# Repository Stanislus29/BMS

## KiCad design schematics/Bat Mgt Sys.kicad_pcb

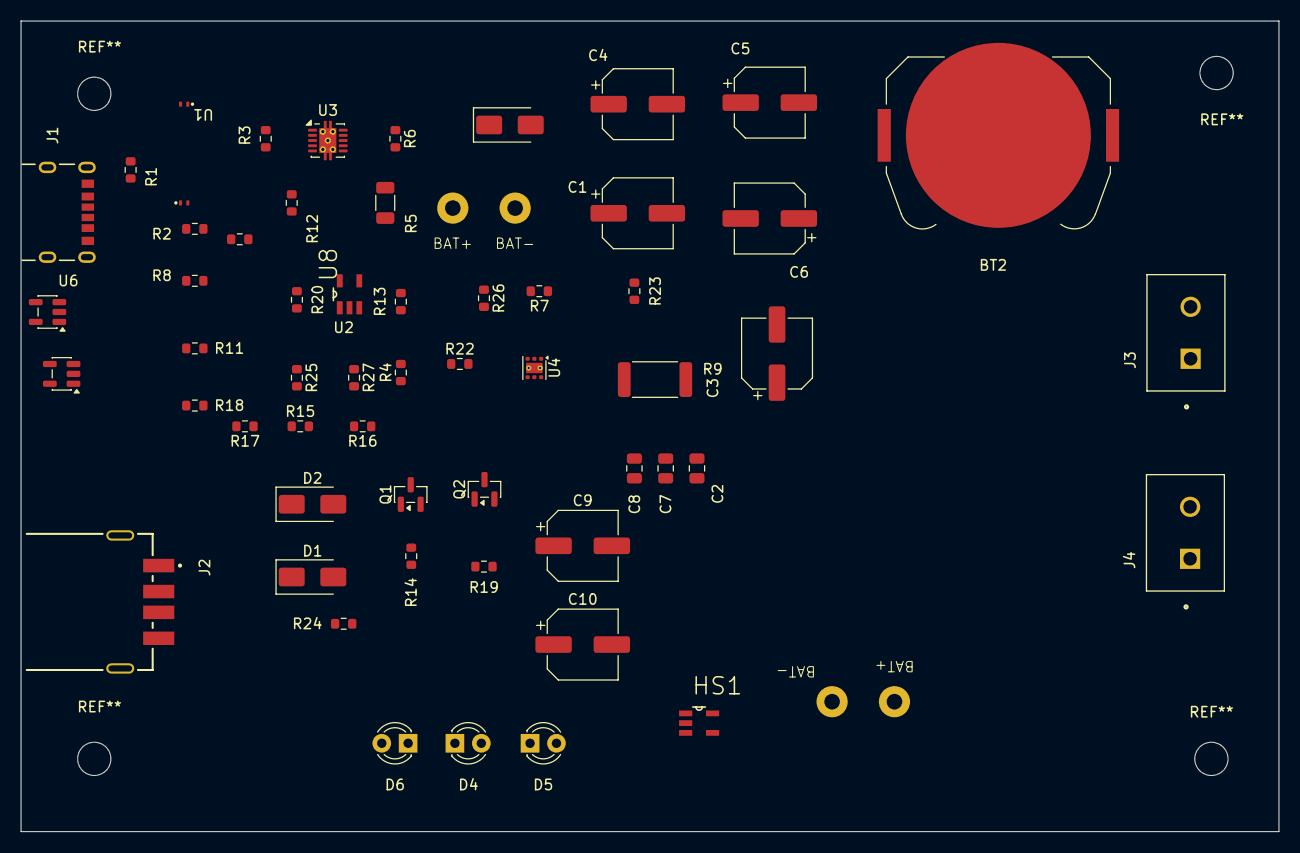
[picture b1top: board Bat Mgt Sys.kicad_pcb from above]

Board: 4 copper layers, 121.0 x 78.0 mm, 59 parts (0 on the bottom side), 29 nets, no tracks yet.

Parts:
BT1: Battery; THROUGH_HOLES
BT2: 2.0; BatteryHolder_Keystone_3034_1x20mm
C1, C4, C6: 100u; CP_Elec_6.3x5.4
C2: 0.1u; C_0805_2012Metric
C3: 22n; CP_Elec_6.3x5.4
C5: 4700u; CP_Elec_6.3x5.4
C7, C8: 10u; C_0805_2012Metric
C9, C10: 22; CP_Elec_6.3x5.4
D1, D2, D3: SS14; D_SMA
D4: GREEN; LED_D3.0mm
D5: RED; LED_D3.0mm
D6: WHITE; LED_D3.0mm
HS1: 5.8 W/mK; SOT95P280X140-5N
J1: USB_C_Receptacle_PowerOnly_6P; MOLEX_2171750001
J2: USB_A; GCT_USB1046-GF-0190-L-B-A_REVB4
J3, J4: Screw_Terminal_01x02; OST_OSTTC020162
Q1, Q2: IRLML6402; SOT-23
R1, R2: 5.1K; R_0603_1608Metric
R3: 1M; R_0603_1608Metric
R4: 453k; R_0603_1608Metric
R5: 1; R_1206_3216Metric
R6: 76.8k; R_0603_1608Metric
R7: 42.25k; R_0603_1608Metric
R8, R14, R15, R16, R18, R22, R24: 10k; R_0603_1608Metric
R9: 0.885; R_2512_6332Metric
R11: 11.2k; R_0603_1608Metric
R12: 6.6k; R_0603_1608Metric
R13: 10K; R_0603_1608Metric
R17: 3.8k; R_0603_1608Metric
R19: 100; R_0603_1608Metric
R20: 96k; R_0603_1608Metric
R21: 73.2k; R_0603_1608Metric
R23: 5k; R_0603_1608Metric
R25: 1.45k; R_0603_1608Metric
R26: 1.6k; R_0603_1608Metric
R27: 370; R_0603_1608Metric
Thermistor(NXRT15XV103FA3A016)1: 10K; THROUGH_HOLES
U1, U2: TPD1E05U06DPY; Texas_DPY0002A_0.6x1mm_P0.65mm
U3: TPS2592xx; VSON-10-1EP_3x3mm_P0.5mm_EP1.65x2.4mm_ThermalVias
U4: TLV76701DRVx; WSON-6-1EP_2x2mm_P0.65mm_EP1x1.6mm_ThermalVias
U5, U6: MCP6561-OT; SOT-23-5
U8: 74AHC1G02W5-7; SOT95P280X140-5N

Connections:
+BAT: BT1.1 (+), D3.1 (K), Q1.2 (S), R12.1
+BOUT: C9.1, D1.2 (A), J4.1, Q2.3 (D), R24.1
+POUT: C5.2, C6.1, C10.1, D2.2 (A), J3.1, Q1.1 (G), R5.1, R15.1, R17.1, Thermistor(NXRT15XV103FA3A016)1.1, U4.6 (IN), U5.5 (V+), U6.5 (V+), U8.5 (VCC)
/IN: C2.1, J1.A9 (VBUS), J1.B9 (VBUS), R3.1, U3.3 (VIN), U3.4 (VIN), U3.5 (VIN)
/SYS: D1.1 (K), D2.1 (K), J2.1 (VBUS)
/TH_OUT: R21.2, R26.1, U6.1, U8.2 (B)
/US_OUT: R20.2, R25.1, U5.1, U8.1 (A)
/VOUT: C7.1, R7.1, R9.2, U4.1 (OUT)
/V_REF+: R12.2, R13.2, R20.1, U5.3 (+)
/V_REF-: R15.2, R16.2, U5.4 (-)
/V_d1: Q1.3 (D), R14.1, R19.2
GND: BT1.2 (-), BT2.2 (-), C1.2, C2.2, C3.1, C4.2, C5.1, C6.2, C7.2, C8.2, C9.2, C10.2, D4.1 (K), D5.1 (K), D6.1 (K), J1.A12 (GND), J1.B12 (GND), J2.4 (GND), J3.2, J4.2, R1.2, R2.2, R4.2, R6.2, R8.2, R11.1, R13.1, R14.2, R16.1, R18.1, R22.1, R24.2, U1.2 (GND), U2.2 (GND), U3.11 (GND), U4.3 (GND), U4.5 (GND), U4.7 (PAD), U5.2 (V-), U6.2 (V-), U8.3 (GND)
unnamed: BT2.1 (+), R23.1
unnamed: C8.1, D3.2 (A), R9.1
unnamed: D4.2 (A), R25.2
unnamed: D5.2 (A), R26.2
unnamed: D6.2 (A), R27.2
unnamed: J1.A5 (CC1), R1.1, U2.1 (I/O)
unnamed: J1.B5 (CC2), R2.1, U1.1 (I/O)
unnamed: Q2.1 (G), R22.2, R23.2
unnamed: Q2.2 (S), R19.1
unnamed: R5.2, U3.6 (OUT), U3.7 (OUT), U3.8 (OUT)
unnamed: R3.2, R4.1, U3.2 (EN/UVLO)
unnamed: R6.1, U3.10 (ILIM)
unnamed: C3.2, U3.1 (dV/dT)
unnamed: R7.2, R8.1, U4.2 (FB)
unnamed: R11.2, R21.1, Thermistor(NXRT15XV103FA3A016)1.2, U6.3 (+)
unnamed: R17.2, R18.2, U6.4 (-)
VIN: R27.1, U4.4 (EN), U8.4 (Y)

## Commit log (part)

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2026-06-17 trying to figure out sim issue with MCP6561
2026-06-19 working on sim files, made updates to sim models, trying to fix issue on linux
2026-06-19 Update schematics, add custom footprints, 3D models, and gitignore
2026-06-19 simulations fixed with solid model files, results documented
2026-06-29 updated simulation parameters, and adjusted file locations
2026-06-30 check folder lm311 for comparator schematics
